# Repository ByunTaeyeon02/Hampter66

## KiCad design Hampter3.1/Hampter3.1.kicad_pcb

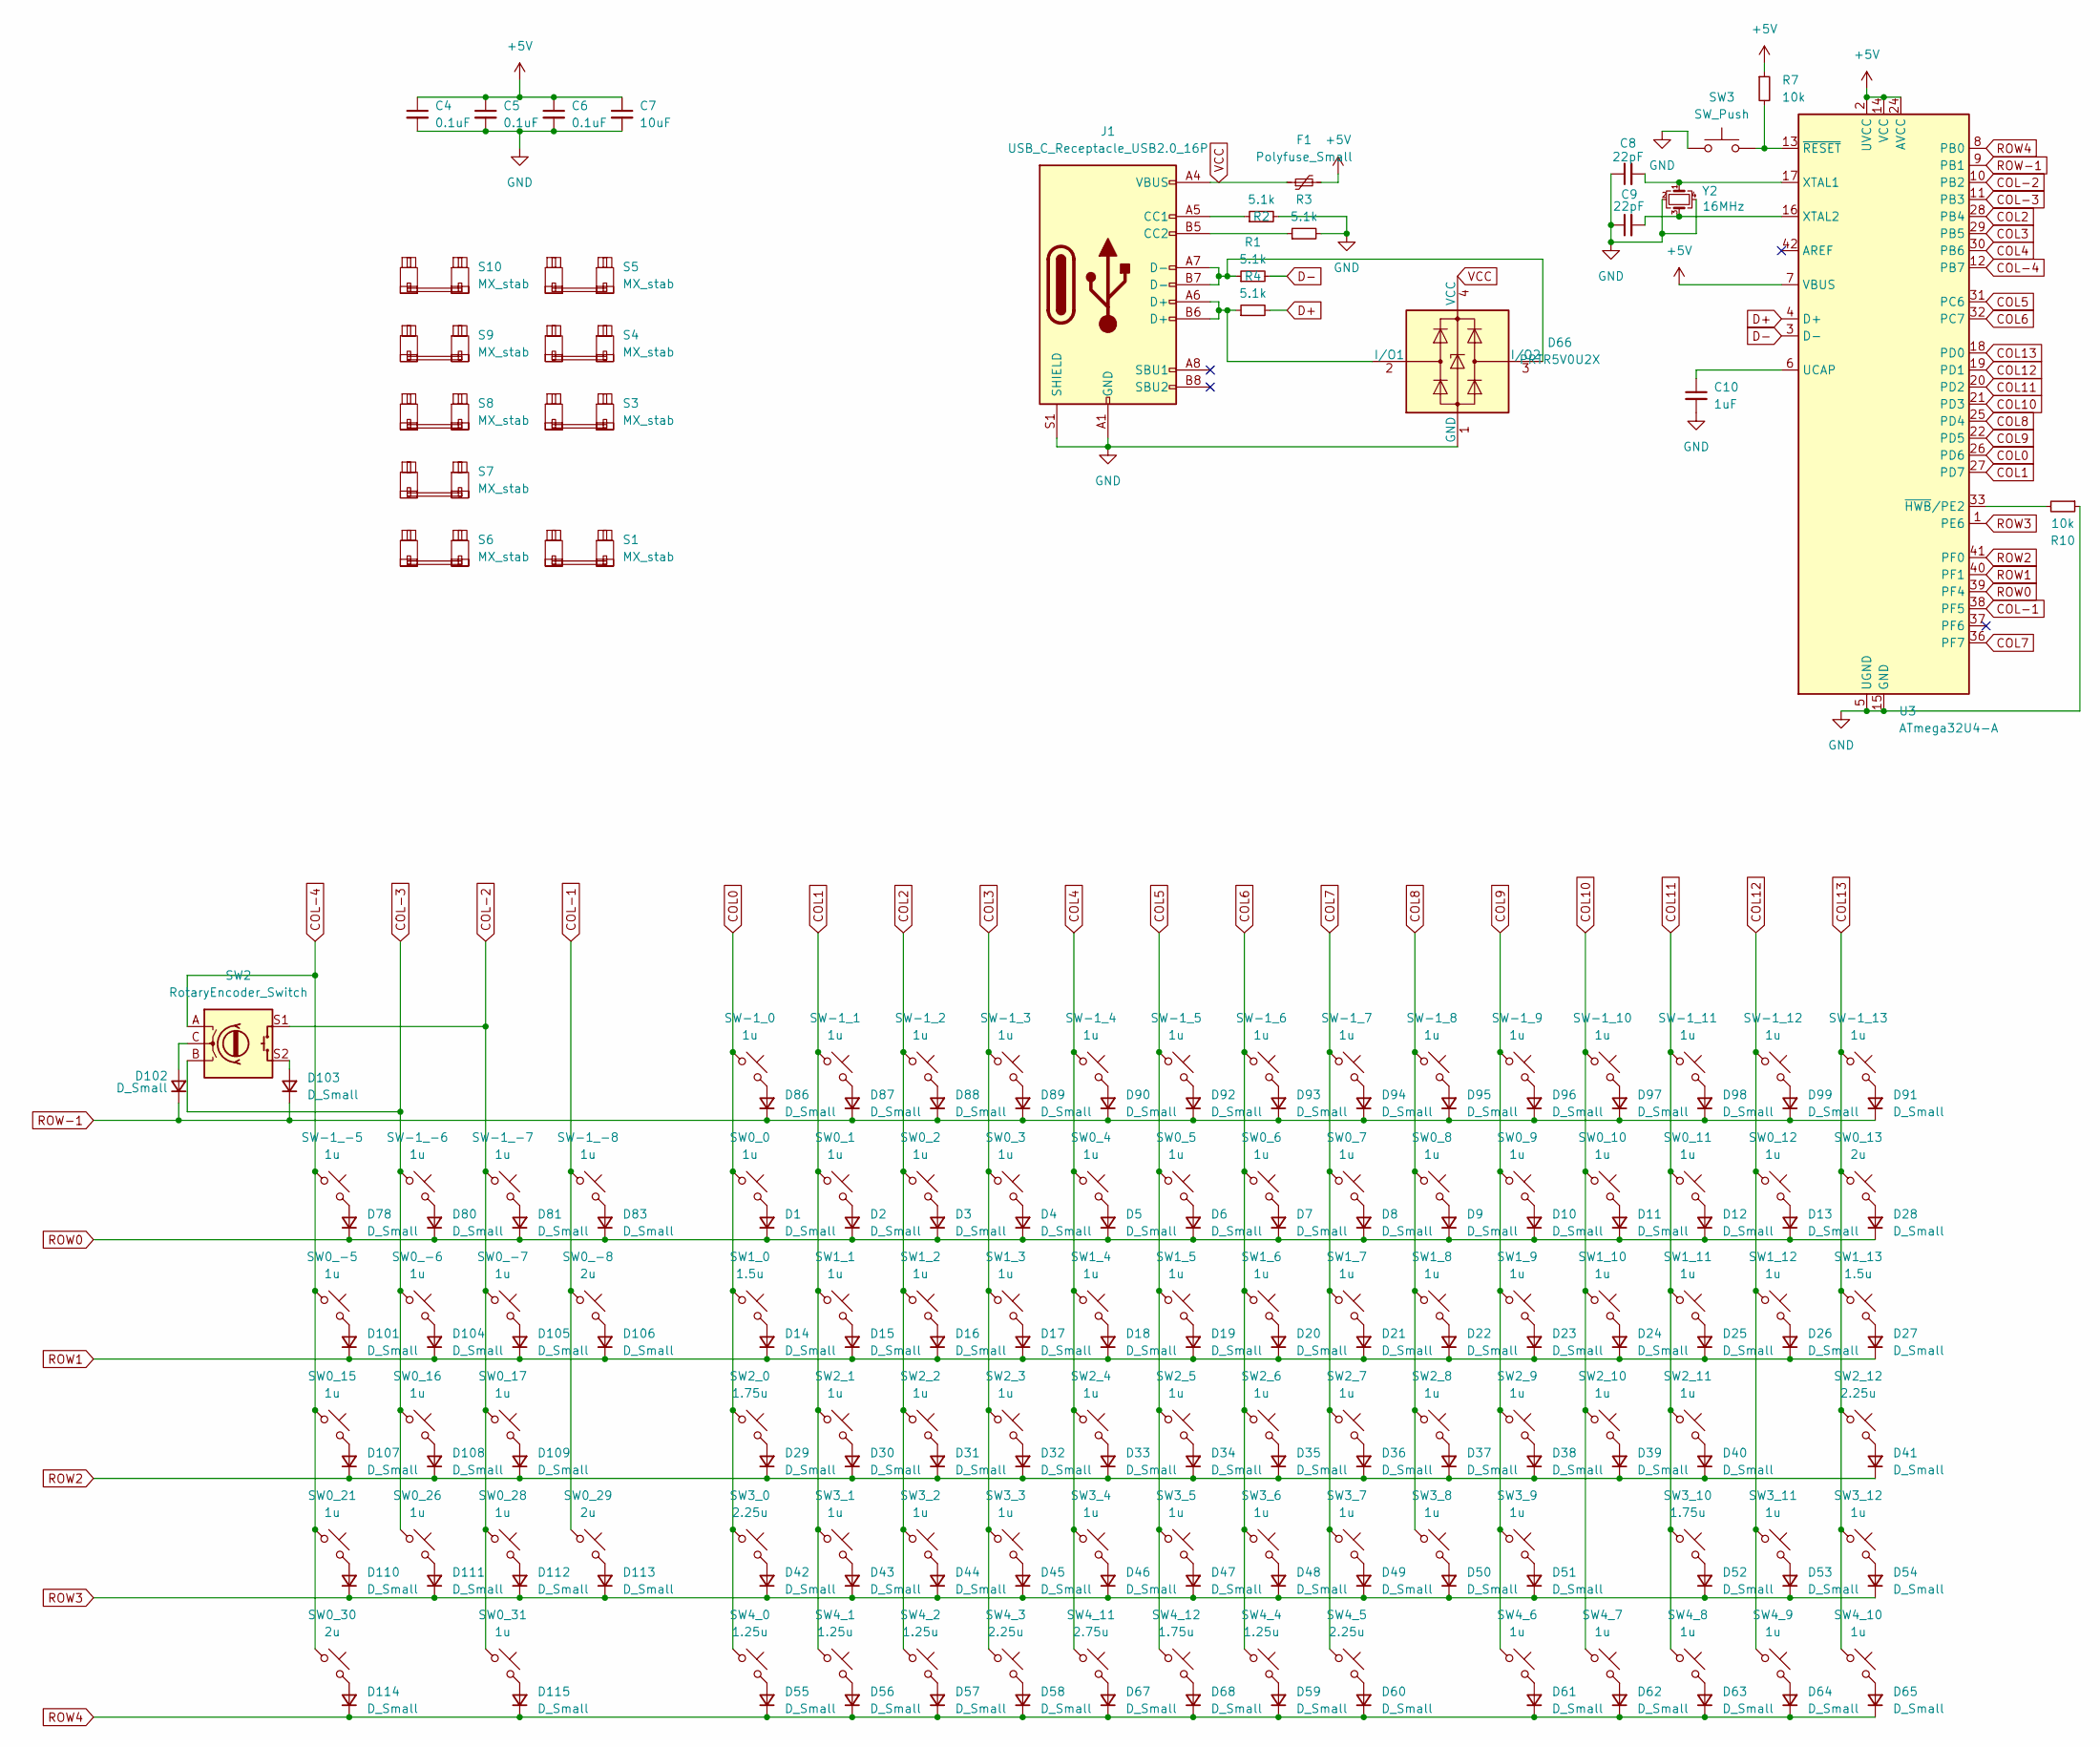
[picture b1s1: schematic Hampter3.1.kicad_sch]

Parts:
C4, C5, C6: 0.1uF; R_0805_2012Metric
C7: 10uF; R_0805_2012Metric
C8, C9: 22pF; R_0805_2012Metric
C10: 1uF; R_0805_2012Metric
D1, D2, D3, D4, D5, D6, D7, D8, D9, D10, D11, D12, D13, D14, D15, D16, D17, D18, D19, D20, D21, D22, D23, D24, D25, D26, D27, D28, D29, D30, D31, D32, D33, D34, D35, D36, D37, D38, D39, D40, D41, D42, D43, D44, D45, D46, D47, D48, D49, D50, D51, D52, D53, D54, D55, D56, D57, D58, D59, D60, D61, D62, D63, D64, D65, D67, D68, D78, D80, D81, D83, D86, D87, D88, D89, D90, D91, D92, D93, D94, D95, D96, D97, D98, D99, D101, D102, D103, D104, D105, D106, D107, D108, D109, D110, D111, D112, D113, D114, D115: D_Small; D_SOD-123
D66: PRTR5V0U2X; SOT-143
F1: Polyfuse_Small; Fuse_1206_3216Metric_Pad1.42x1.75mm_HandSolder
J1: USB_C_Receptacle_USB2.0_16P; USB_C_Receptacle_HRO_TYPE-C-31-M-12
R1, R2, R3, R4: 5.1k; R_0805_2012Metric
R7, R10: 10k; R_0805_2012Metric
S1, S3, S4, S9: MX_stab; STAB_MX_2.25u
S5, S6, S7, S8: MX_stab; STAB_MX_2u
S10: MX_stab; STAB_MX_2.75u
SW0_0, SW0_1, SW0_2, SW0_3, SW0_4, SW0_5, SW0_6, SW0_7, SW0_8, SW0_9, SW0_10, SW0_11, SW0_12, SW0_15, SW0_16, SW0_17, SW0_21, SW0_26, SW0_28, SW0_31, SW0_-5, SW0_-6, SW0_-7, SW1_1, SW1_2, SW1_3, SW1_4, SW1_5, SW1_6, SW1_7, SW1_8, SW1_9, SW1_10, SW1_11, SW1_12, SW2_1, SW2_2, SW2_3, SW2_4, SW2_5, SW2_6, SW2_7, SW2_8, SW2_9, SW2_10, SW2_11, SW3_1, SW3_2, SW3_3, SW3_4, SW3_5, SW3_6, SW3_7, SW3_8, SW3_9, SW3_11, SW3_12, SW4_6, SW4_7, SW4_8, SW4_9, SW4_10: 1u; SW_MX_1u
SW0_13, SW0_29, SW0_30, SW0_-8: 2u; SW_MX_1u
SW1_0, SW1_13: 1.5u; SW_MX_1.5u
SW2: RotaryEncoder_Switch; RotaryEncoder_Alps_EC11E-Switch_Vertical_H20mm
SW2_0, SW3_10, SW4_12: 1.75u; SW_MX_1.75u
SW2_12, SW3_0, SW4_3, SW4_5: 2.25u; SW_MX_1u
SW3: SW_Push; SW_SPST_SKQG_WithStem
SW4_0, SW4_1, SW4_2, SW4_4: 1.25u; SW_MX_1.25u
SW4_11: 2.75u; SW_MX_1u
SW-1_0, SW-1_1, SW-1_2, SW-1_3, SW-1_4, SW-1_5, SW-1_6, SW-1_7, SW-1_8, SW-1_9, SW-1_10, SW-1_11, SW-1_12, SW-1_13, SW-1_-5, SW-1_-6, SW-1_-7, SW-1_-8: 1u; SW_MX_1u
U3: ATmega32U4-A; TQFP-44_10x10mm_P0.8mm
Y2: 16MHz; Crystal_SMD_3225-4Pin_3.2x2.5mm

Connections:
+5V: C4.1, C5.1, C6.1, C7.1, F1.2, R7.1, U3.2 (UVCC), U3.7 (VBUS), U3.14 (VCC), U3.24 (AVCC), U3.34 (VCC), U3.44 (AVCC)
COL0: SW0_0.1, SW1_0.1, SW2_0.1, SW3_0.1, SW4_0.1, SW-1_0.1, U3.26 (PD6)
COL1: SW0_1.1, SW1_1.1, SW2_1.1, SW3_1.1, SW4_1.1, SW-1_1.1, U3.27 (PD7)
COL2: SW0_2.1, SW1_2.1, SW2_2.1, SW3_2.1, SW4_2.1, SW-1_2.1, U3.28 (PB4)
COL3: SW0_3.1, SW1_3.1, SW2_3.1, SW3_3.1, SW4_3.1, SW-1_3.1, U3.29 (PB5)
COL4: SW0_4.1, SW1_4.1, SW2_4.1, SW3_4.1, SW4_11.1, SW-1_4.1, U3.30 (PB6)
COL5: SW0_5.1, SW1_5.1, SW2_5.1, SW3_5.1, SW4_12.1, SW-1_5.1, U3.31 (PC6)
COL6: SW0_6.1, SW1_6.1, SW2_6.1, SW3_6.1, SW4_4.1, SW-1_6.1, U3.32 (PC7)
COL7: SW0_7.1, SW1_7.1, SW2_7.1, SW3_7.1, SW4_5.1, SW-1_7.1, U3.36 (PF7)
COL8: SW0_8.1, SW1_8.1, SW2_8.1, SW3_8.1, SW-1_8.1, U3.25 (PD4)
COL9: SW0_9.1, SW1_9.1, SW2_9.1, SW3_9.1, SW4_6.1, SW-1_9.1, U3.22 (PD5)
COL10: SW0_10.1, SW1_10.1, SW2_10.1, SW4_7.1, SW-1_10.1, U3.21 (PD3)
COL11: SW0_11.1, SW1_11.1, SW2_11.1, SW3_10.1, SW4_8.1, SW-1_11.1, U3.20 (PD2)
COL12: SW0_12.1, SW1_12.1, SW3_11.1, SW4_9.1, SW-1_12.1, U3.19 (PD1)
COL13: SW0_13.1, SW1_13.1, SW2_12.1, SW3_12.1, SW4_10.1, SW-1_13.1, U3.18 (PD0)
COL-1: SW0_29.1, SW0_-8.1, SW-1_-8.1, U3.38 (PF5)
COL-2: SW0_17.1, SW0_28.1, SW0_31.1, SW0_-7.1, SW2.S1, SW-1_-7.1, U3.10 (PB2)
COL-3: SW0_16.1, SW0_26.1, SW0_-6.1, SW2.B, SW-1_-6.1, U3.11 (PB3)
COL-4: SW0_15.1, SW0_21.1, SW0_30.1, SW0_-5.1, SW2.A, SW-1_-5.1, U3.12 (PB7)
D+: R4.2, U3.4 (D+)
D-: R1.2, U3.3 (D-)
GND: C4.2, C5.2, C6.2, C7.2, C8.1, C9.1, C10.2, D66.1 (GND), J1.A1 (GND), J1.A12 (GND), J1.B1 (GND), J1.B12 (GND), J1.S1 (SHIELD), R2.2, R3.2, R10.1, SW3.1, U3.5 (UGND), U3.15 (GND), U3.23 (GND), U3.35 (GND), U3.43 (GND), Y2.2, Y2.4
unnamed: D1.2 (A), SW0_0.2
unnamed: D2.2 (A), SW0_1.2
unnamed: D3.2 (A), SW0_2.2
unnamed: D4.2 (A), SW0_3.2
unnamed: D5.2 (A), SW0_4.2
unnamed: D6.2 (A), SW0_5.2
unnamed: D7.2 (A), SW0_6.2
unnamed: D8.2 (A), SW0_7.2
unnamed: D9.2 (A), SW0_8.2
unnamed: D10.2 (A), SW0_9.2
unnamed: D11.2 (A), SW0_10.2
unnamed: D12.2 (A), SW0_11.2
unnamed: D13.2 (A), SW0_12.2
unnamed: D14.2 (A), SW1_0.2
unnamed: D15.2 (A), SW1_1.2
unnamed: D16.2 (A), SW1_2.2
unnamed: D17.2 (A), SW1_3.2
unnamed: D18.2 (A), SW1_4.2
unnamed: D19.2 (A), SW1_5.2
unnamed: D20.2 (A), SW1_6.2
unnamed: D21.2 (A), SW1_7.2
unnamed: D22.2 (A), SW1_8.2
unnamed: D23.2 (A), SW1_9.2
unnamed: D24.2 (A), SW1_10.2
unnamed: D25.2 (A), SW1_11.2
unnamed: D26.2 (A), SW1_12.2
unnamed: D27.2 (A), SW1_13.2
unnamed: D28.2 (A), SW0_13.2
unnamed: D29.2 (A), SW2_0.2
unnamed: D30.2 (A), SW2_1.2
unnamed: D31.2 (A), SW2_2.2
unnamed: D32.2 (A), SW2_3.2
unnamed: D33.2 (A), SW2_4.2
unnamed: D34.2 (A), SW2_5.2
unnamed: D35.2 (A), SW2_6.2
unnamed: D36.2 (A), SW2_7.2
unnamed: D37.2 (A), SW2_8.2
unnamed: D38.2 (A), SW2_9.2
unnamed: D39.2 (A), SW2_10.2
unnamed: D40.2 (A), SW2_11.2
unnamed: D41.2 (A), SW2_12.2
unnamed: D42.2 (A), SW3_0.2
unnamed: D43.2 (A), SW3_1.2
unnamed: D44.2 (A), SW3_2.2
unnamed: D45.2 (A), SW3_3.2
unnamed: D46.2 (A), SW3_4.2
unnamed: D47.2 (A), SW3_5.2
unnamed: D48.2 (A), SW3_6.2
unnamed: D49.2 (A), SW3_7.2
unnamed: D50.2 (A), SW3_8.2
unnamed: D51.2 (A), SW3_9.2
unnamed: D52.2 (A), SW3_10.2
unnamed: D53.2 (A), SW3_11.2
unnamed: D54.2 (A), SW3_12.2
unnamed: D55.2 (A), SW4_0.2
unnamed: D56.2 (A), SW4_1.2
unnamed: D57.2 (A), SW4_2.2
unnamed: D58.2 (A), SW4_3.2
unnamed: D59.2 (A), SW4_4.2
unnamed: D60.2 (A), SW4_5.2
unnamed: D61.2 (A), SW4_6.2
unnamed: D62.2 (A), SW4_7.2
unnamed: D63.2 (A), SW4_8.2
unnamed: D64.2 (A), SW4_9.2
unnamed: D65.2 (A), SW4_10.2
unnamed: D66.2 (I/O1), J1.A6 (D+), J1.B6 (D+), R4.1
unnamed: D66.3 (I/O2), J1.A7 (D-), J1.B7 (D-), R1.1
unnamed: D67.2 (A), SW4_11.2
unnamed: D68.2 (A), SW4_12.2
unnamed: D78.2 (A), SW-1_-5.2
unnamed: D80.2 (A), SW-1_-6.2
unnamed: D81.2 (A), SW-1_-7.2
unnamed: D83.2 (A), SW-1_-8.2
unnamed: D86.2 (A), SW-1_0.2
unnamed: D87.2 (A), SW-1_1.2
unnamed: D88.2 (A), SW-1_2.2
unnamed: D89.2 (A), SW-1_3.2
unnamed: D90.2 (A), SW-1_4.2
unnamed: D91.2 (A), SW-1_13.2
unnamed: D92.2 (A), SW-1_5.2
unnamed: D93.2 (A), SW-1_6.2
unnamed: D94.2 (A), SW-1_7.2
unnamed: D95.2 (A), SW-1_8.2
unnamed: D96.2 (A), SW-1_9.2
unnamed: D97.2 (A), SW-1_10.2
unnamed: D98.2 (A), SW-1_11.2
unnamed: D99.2 (A), SW-1_12.2
unnamed: D101.2 (A), SW0_-5.2
unnamed: D102.2 (A), SW2.C
unnamed: D103.2 (A), SW2.S2
unnamed: D104.2 (A), SW0_-6.2
unnamed: D105.2 (A), SW0_-7.2
unnamed: D106.2 (A), SW0_-8.2
unnamed: D107.2 (A), SW0_15.2
unnamed: D108.2 (A), SW0_16.2
unnamed: D109.2 (A), SW0_17.2
unnamed: D110.2 (A), SW0_21.2
unnamed: D111.2 (A), SW0_26.2
unnamed: D112.2 (A), SW0_28.2
unnamed: D113.2 (A), SW0_29.2
unnamed: D114.2 (A), SW0_30.2
unnamed: D115.2 (A), SW0_31.2
unnamed: J1.A5 (CC1), R2.1
unnamed: J1.B5 (CC2), R3.1
unnamed: C10.1, U3.6 (UCAP)
unnamed: C8.2, U3.17 (XTAL1), Y2.1
unnamed: C9.2, U3.16 (XTAL2), Y2.3
unnamed: R10.2, U3.33 (~HWB/PE2)
unnamed: R7.2, SW3.2, U3.13 (~RESET)
ROW0: D1.1 (K), D2.1 (K), D3.1 (K), D4.1 (K), D5.1 (K), D6.1 (K), D7.1 (K), D8.1 (K), D9.1 (K), D10.1 (K), D11.1 (K), D12.1 (K), D13.1 (K), D28.1 (K), D78.1 (K), D80.1 (K), D81.1 (K), D83.1 (K), U3.39 (PF4)
ROW1: D14.1 (K), D15.1 (K), D16.1 (K), D17.1 (K), D18.1 (K), D19.1 (K), D20.1 (K), D21.1 (K), D22.1 (K), D23.1 (K), D24.1 (K), D25.1 (K), D26.1 (K), D27.1 (K), D101.1 (K), D104.1 (K), D105.1 (K), D106.1 (K), U3.40 (PF1)
ROW2: D29.1 (K), D30.1 (K), D31.1 (K), D32.1 (K), D33.1 (K), D34.1 (K), D35.1 (K), D36.1 (K), D37.1 (K), D38.1 (K), D39.1 (K), D40.1 (K), D41.1 (K), D107.1 (K), D108.1 (K), D109.1 (K), U3.41 (PF0)
ROW3: D42.1 (K), D43.1 (K), D44.1 (K), D45.1 (K), D46.1 (K), D47.1 (K), D48.1 (K), D49.1 (K), D50.1 (K), D51.1 (K), D52.1 (K), D53.1 (K), D54.1 (K), D110.1 (K), D111.1 (K), D112.1 (K), D113.1 (K), U3.1 (PE6)
ROW4: D55.1 (K), D56.1 (K), D57.1 (K), D58.1 (K), D59.1 (K), D60.1 (K), D61.1 (K), D62.1 (K), D63.1 (K), D64.1 (K), D65.1 (K), D67.1 (K), D68.1 (K), D114.1 (K), D115.1 (K), U3.8 (PB0)
ROW-1: D86.1 (K), D87.1 (K), D88.1 (K), D89.1 (K), D90.1 (K), D91.1 (K), D92.1 (K), D93.1 (K), D94.1 (K), D95.1 (K), D96.1 (K), D97.1 (K), D98.1 (K), D99.1 (K), D102.1 (K), D103.1 (K), U3.9 (PB1)
VCC: D66.4 (VCC), F1.1, J1.A4 (VBUS), J1.A9 (VBUS), J1.B4 (VBUS), J1.B9 (VBUS)

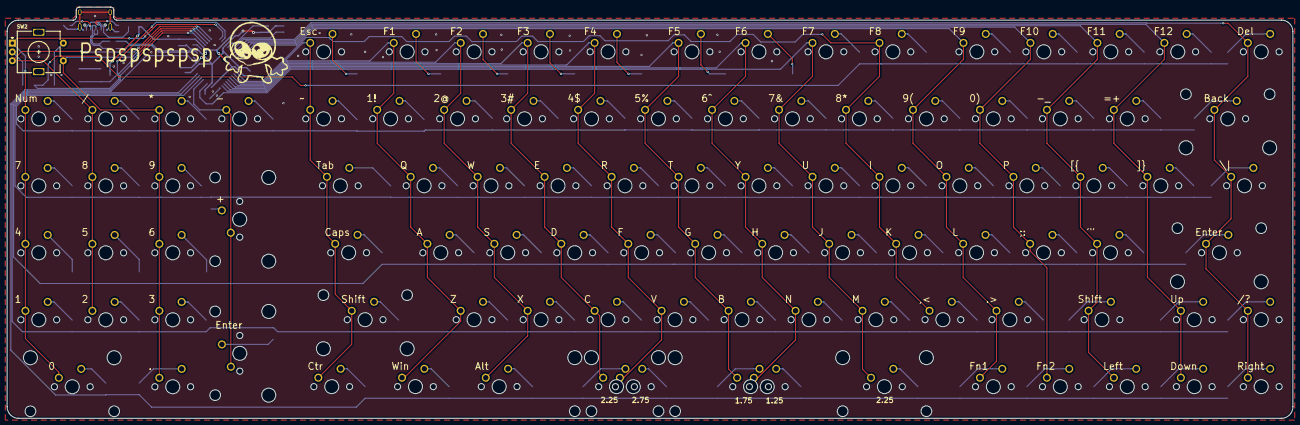
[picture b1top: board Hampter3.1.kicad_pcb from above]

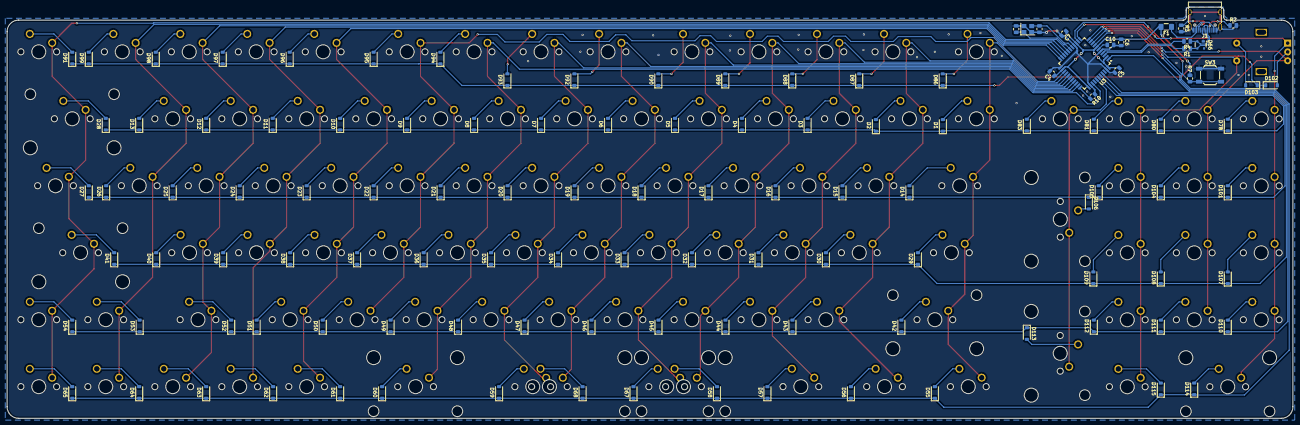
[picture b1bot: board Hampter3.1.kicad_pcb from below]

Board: 2 copper layers, 365.7 x 117.0 mm, 227 parts (119 on the bottom side), 138 nets.

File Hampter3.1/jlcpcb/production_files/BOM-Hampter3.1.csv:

Comment,Designator,Footprint,LCSC,Quantity
Polyfuse_Small,F1,Fuse_1206_3216Metric_Pad1.42x1.75mm_HandSolder,C1048,1
PRTR5V0U2X,D66,SOT-143,C12333,1
16MHz,Y2,Crystal_SMD_3225-4Pin_3.2x2.5mm,C13738,1
0.1uF,"C4,C5,C6",R_0805_2012Metric,C141124,3
10uF,C7,R_0805_2012Metric,C15850,1
10k,"R10,R7",R_0805_2012Metric,C17414,2
22pF,"C8,C9",R_0805_2012Metric,C1804,2
5.1k,"R1,R2,R3,R4",R_0805_2012Metric,C27834,4
1uF,C10,R_0805_2012Metric,C28323,1
USB_C_Receptacle_USB2.0_16P,J1,USB_C_Receptacle_HRO_TYPE-C-31-M-12,C37616412,1
ATmega32U4-A,U3,TQFP-44_10x10mm_P0.8mm,C44854,1
D_Small,"D1,D10,D101,D102,D103,D104,D105,D106,D107,D108,D109,D11,D110,D111,D112,D113,D114,D115,D12,D13,D14,D15,D16,D17,D18,D19,D2,D20,D21,D22,D23,D24,D25,D26,D27,D28,D29,D3,D30,D31,D32,D33,D34,D35,D36,D37,D38,D39,D4,D40,D41,D42,D43,D44,D45,D46,D47,D48,D49,D5,D50,D51,D52,D53,D54,D55,D56,D57,D58,D59,D6,D60,D61,D62,D63,D64,D65,D67,D68,D7,D78,D8,D80,D81,D83,D86,D87,D88,D89,D9,D90,D91,D92,D93,D94,D95,D96,D97,D98,D99",D_SOD-123,C552328,100
SW_Push,SW3,SW_SPST_SKQG_WithStem,C97448,1

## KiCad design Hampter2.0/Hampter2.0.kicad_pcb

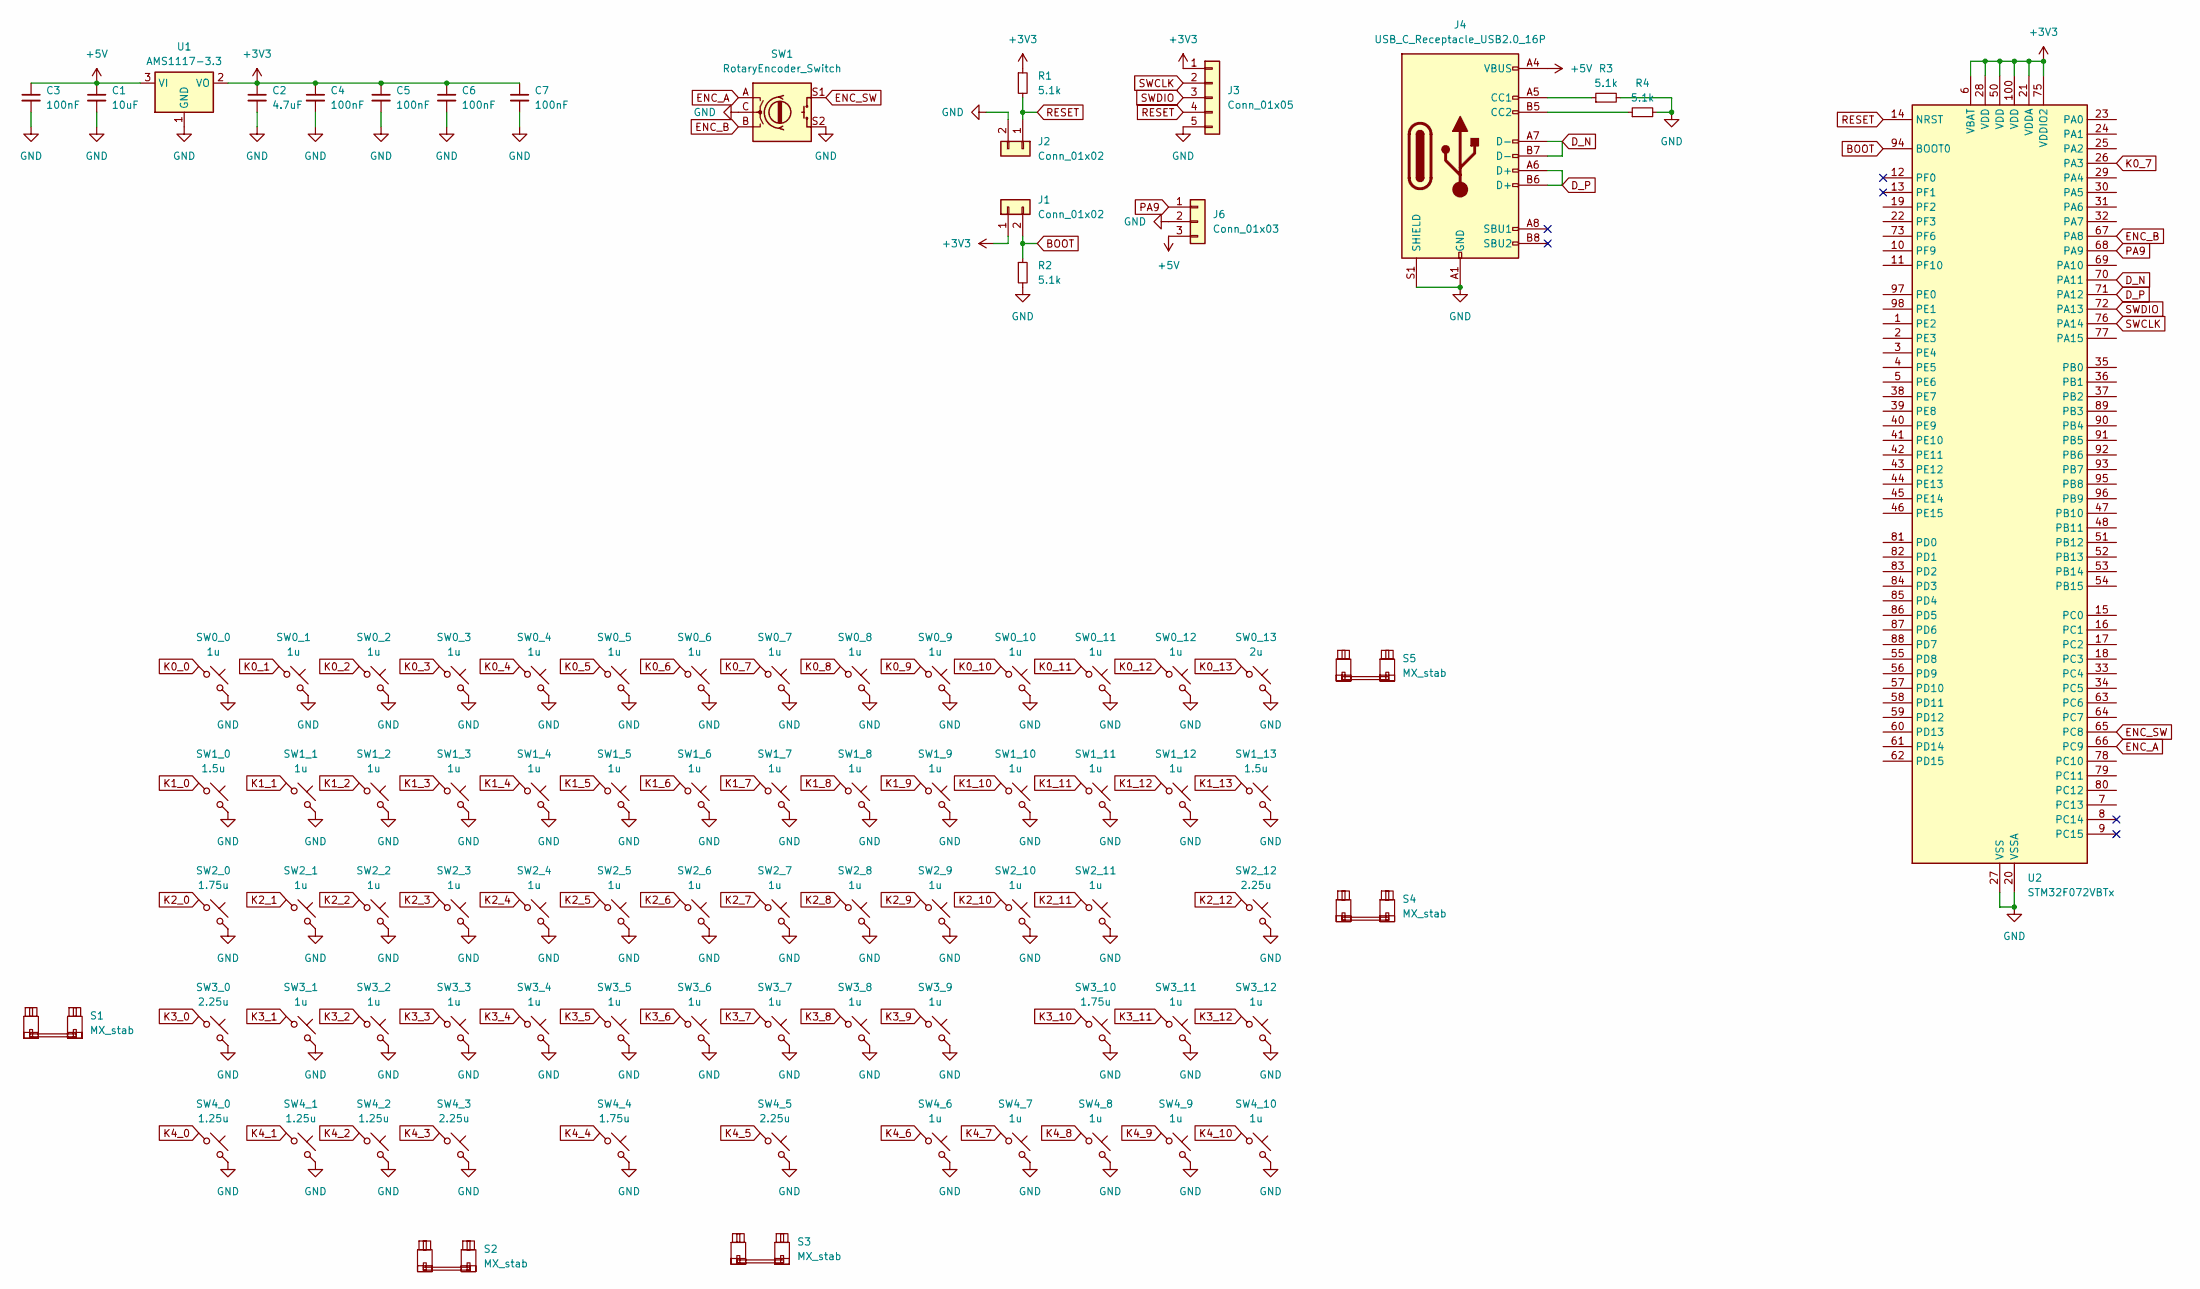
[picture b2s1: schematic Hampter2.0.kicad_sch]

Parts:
C1: 10uF; C_0603_1608Metric
C2: 4.7uF; C_0603_1608Metric
C3, C4, C5, C6, C7: 100nF; C_0603_1608Metric
J1, J2: Conn_01x02; PinHeader_1x02_P2.54mm_Vertical
J3: Conn_01x05; PinHeader_1x05_P2.54mm_Vertical
J4: USB_C_Receptacle_USB2.0_16P; USB_C_Receptacle_GCT_USB4085
J6: Conn_01x03; PinHeader_1x03_P2.54mm_Vertical
R1, R2, R3, R4: 5.1k; R_0603_1608Metric
S1, S2, S3, S4: MX_stab; STAB_MX_P_2.25u
S5: MX_stab; STAB_MX_P_2u
SW0_0, SW0_1, SW0_2, SW0_3, SW0_4, SW0_5, SW0_6, SW0_7, SW0_8, SW0_9, SW0_10, SW0_11, SW0_12, SW1_1, SW1_2, SW1_3, SW1_4, SW1_5, SW1_6, SW1_7, SW1_8, SW1_9, SW1_10, SW1_11, SW1_12, SW2_1, SW2_2, SW2_3, SW2_4, SW2_5, SW2_6, SW2_7, SW2_8, SW2_9, SW2_10, SW2_11, SW3_1, SW3_2, SW3_3, SW3_4, SW3_5, SW3_6, SW3_7, SW3_8, SW3_9, SW3_11, SW3_12, SW4_6, SW4_7, SW4_8, SW4_9, SW4_10: 1u; SW_MX_HS_CPG151101S11_1u
SW0_13: 2u; SW_MX_HS_CPG151101S11_1u
SW1: RotaryEncoder_Switch; RotaryEncoder_Alps_EC11E-Switch_Vertical_H20mm
SW1_0, SW1_13: 1.5u; SW_MX_HS_CPG151101S11_1.5u
SW2_0, SW3_10, SW4_4: 1.75u; SW_MX_HS_CPG151101S11_1.75u
SW2_12, SW3_0, SW4_3, SW4_5: 2.25u; SW_MX_HS_CPG151101S11_1u
SW4_0, SW4_1, SW4_2: 1.25u; SW_MX_HS_CPG151101S11_1.25u
U1: AMS1117-3.3; SOT-223-3_TabPin2
U2: STM32F072VBTx; LQFP-100_14x14mm_P0.5mm

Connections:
+3V3: C2.1, C4.1, C5.1, C6.1, C7.1, J1.1, J3.1, R1.1, U1.2 (VO), U2.6 (VBAT), U2.21 (VDDA), U2.28 (VDD), U2.50 (VDD), U2.75 (VDDIO2), U2.100 (VDD)
+5V: C1.1, C3.1, J4.A4 (VBUS), J4.A9 (VBUS), J4.B4 (VBUS), J4.B9 (VBUS), J6.3, U1.3 (VI)
BOOT: J1.2, R2.1, U2.94 (BOOT0)
D_N: J4.A7 (D-), J4.B7 (D-), U2.70 (PA11)
D_P: J4.A6 (D+), J4.B6 (D+), U2.71 (PA12)
ENC_A: SW1.A, U2.66 (PC9)
ENC_B: SW1.B, U2.67 (PA8)
ENC_SW: SW1.S1, U2.65 (PC8)
GND: C1.2, C2.2, C3.2, C4.2, C5.2, C6.2, C7.2, J2.2, J3.5, J4.A1 (GND), J4.A12 (GND), J4.B1 (GND), J4.B12 (GND), J4.S1 (SHIELD), J6.2, R2.2, R3.2, R4.2, SW0_0.2, SW0_1.2, SW0_2.2, SW0_3.2, SW0_4.2, SW0_5.2, SW0_6.2, SW0_7.2, SW0_8.2, SW0_9.2, SW0_10.2, SW0_11.2, SW0_12.2, SW0_13.2, SW1.C, SW1.S2, SW1_0.2, SW1_1.2, SW1_2.2, SW1_3.2, SW1_4.2, SW1_5.2, SW1_6.2, SW1_7.2, SW1_8.2, SW1_9.2, SW1_10.2, SW1_11.2, SW1_12.2, SW1_13.2, SW2_0.2, SW2_1.2, SW2_2.2, SW2_3.2, SW2_4.2, SW2_5.2, SW2_6.2, SW2_7.2, SW2_8.2, SW2_9.2, SW2_10.2, SW2_11.2, SW2_12.2, SW3_0.2, SW3_1.2, SW3_2.2, SW3_3.2, SW3_4.2, SW3_5.2, SW3_6.2, SW3_7.2, SW3_8.2, SW3_9.2, SW3_10.2, SW3_11.2, SW3_12.2, SW4_0.2, SW4_1.2, SW4_2.2, SW4_3.2, SW4_4.2, SW4_5.2, SW4_6.2, SW4_7.2, SW4_8.2, SW4_9.2, SW4_10.2, U1.1 (GND), U2.20 (VSSA), U2.27 (VSS), U2.49 (VSS), U2.74 (VSS), U2.99 (VSS)
K0_0: SW0_0.1
K0_1: SW0_1.1
K0_2: SW0_2.1
K0_3: SW0_3.1
K0_4: SW0_4.1
K0_5: SW0_5.1
K0_6: SW0_6.1
K0_7: SW0_7.1, U2.26 (PA3)
K0_8: SW0_8.1
K0_9: SW0_9.1
K0_10: SW0_10.1
K0_11: SW0_11.1
K0_12: SW0_12.1
K0_13: SW0_13.1
K1_0: SW1_0.1
K1_1: SW1_1.1
K1_2: SW1_2.1
K1_3: SW1_3.1
K1_4: SW1_4.1
K1_5: SW1_5.1
K1_6: SW1_6.1
K1_7: SW1_7.1
K1_8: SW1_8.1
K1_9: SW1_9.1
K1_10: SW1_10.1
K1_11: SW1_11.1
K1_12: SW1_12.1
K1_13: SW1_13.1
K2_0: SW2_0.1
K2_1: SW2_1.1
K2_2: SW2_2.1
K2_3: SW2_3.1
K2_4: SW2_4.1
K2_5: SW2_5.1
K2_6: SW2_6.1
K2_7: SW2_7.1
K2_8: SW2_8.1
K2_9: SW2_9.1
K2_10: SW2_10.1
K2_11: SW2_11.1
K2_12: SW2_12.1
K3_0: SW3_0.1
K3_1: SW3_1.1
K3_2: SW3_2.1
K3_3: SW3_3.1
K3_4: SW3_4.1
K3_5: SW3_5.1
K3_6: SW3_6.1
K3_7: SW3_7.1
K3_8: SW3_8.1
K3_9: SW3_9.1
K3_10: SW3_10.1
K3_11: SW3_11.1
K3_12: SW3_12.1
K4_0: SW4_0.1
K4_1: SW4_1.1
K4_2: SW4_2.1
K4_3: SW4_3.1
K4_4: SW4_4.1
K4_5: SW4_5.1
K4_6: SW4_6.1
K4_7: SW4_7.1
K4_8: SW4_8.1
K4_9: SW4_9.1
K4_10: SW4_10.1
unnamed: J4.A5 (CC1), R3.1
unnamed: J4.B5 (CC2), R4.1
PA9: J6.1, U2.68 (PA9)
RESET: J2.1, J3.4, R1.2, U2.14 (NRST)
SWCLK: J3.2, U2.76 (PA14)
SWDIO: J3.3, U2.72 (PA13)

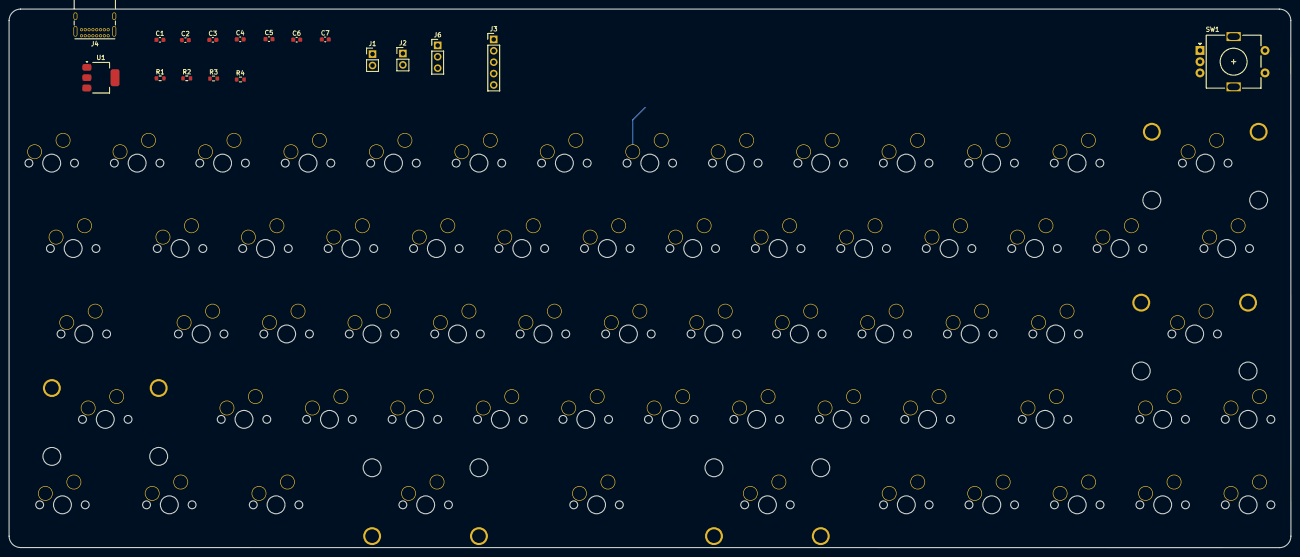
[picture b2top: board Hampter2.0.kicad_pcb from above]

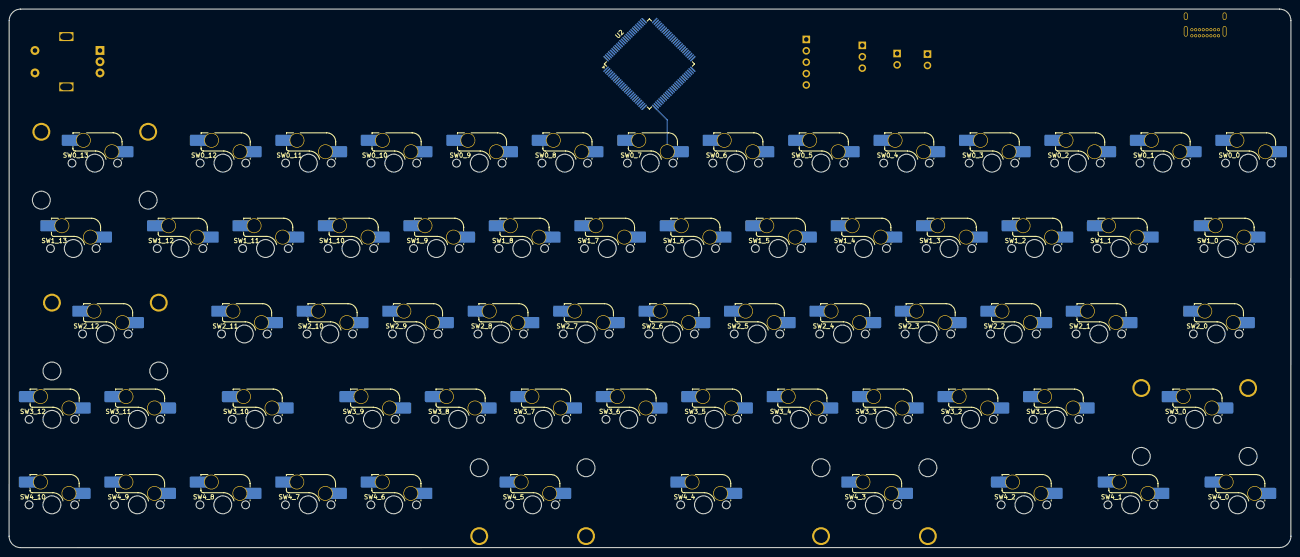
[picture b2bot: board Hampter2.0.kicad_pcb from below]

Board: 2 copper layers, 285.8 x 120.1 mm, 89 parts (66 on the bottom side), 16 nets.
